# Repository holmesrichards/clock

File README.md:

# Clock

This is a clock synth module in Kosmo format. Features are:

* Rotary encoder to set tempo and other parameters.
* Tap button for a different way to set tempo.
* OLED for display of tempo and settings menu.
* 6 outputs: Beat, clock, clock divided by 2, 4, and 8, and clock divided by arbitrary number (between 1 and 64) with offset.
* Two tempo submodes: INC (increment) mode, to set any whole number of beats per minute (BPM) from 8 to 208, and MM (Maelzel Metronome) mode, to more quickly set standard MM values and generalizations of these from 7.5 (= 60 ÷ 8) to 208 BPM.
* Clock pulses per beat (PPB) variable from 1 to 24.
* Clock pulse width (duty cycle) variable from 5% to 95%.
* Interrupt based timer and encoder codes for accuracy.

## Usage

### Pulses and beats

"Beat" is a musical term, referring to the fundamental unit of rhythm, with usually (not always) a quarter note duration corresponding to one beat. "Tempo" refers to how many beats occur per minute.

Since there are shorter notes than quarter notes, this clock can put out multiple — 4 or 8 or some other number — clock pulses per beat.

### Run mode

The module starts up in **run mode**. Here the display shows the tempo in BPM. In a smaller font at the bottom are also shown  PPB and PPM (pulses per minute, which is just PPB times BPM).

At the left, if the clock is running, there is a dot that flashes once per beat.

At the upper left is shown the tempo submode, INC or MM; see below.

In this mode:

* Turning the encoder clockwise or counterclockwise raises or lowers the tempo.
* Tapping the tactile button sets the tempo to match the time between the last two taps.
* Short pressing the encoder stops or restarts the clock.
* A long encoder press switches between INC and MM submodes.
* A long tactile button press switches to **set mode**.

At startup, the tempo is 120 BPM and there are 4 PPB (so the clock speed is 480 pulses per minute).

#### Tempo submodes

In the INC tempo submode, any whole number of BPM from 8 to 208 may be set. When using the encoder, turning one step clockwise or counterclockwise steps to the next higher or lower whole number. When using the tap button, the tap interval is converted to the nearest whole number BPM.

In the MM submode, the tempo is constrained to a generalized version of the usual Maelzel metronome markings, which are

<pre><span style="font-size: 10px">
|     |     |     |     |     |     |  40 |  42 |  44 |  46 |  48 |  50 |  52 |  54 |  56 |  58 |
|  60 |  63 |  66 |  69 |  72 |  76 |  80 |  84 |  88 |  92 |  96 | 100 | 104 | 108 | 112 | 116 |
| 120 | 126 | 132 | 138 | 144 | 152 | 160 | 168 | 176 | 184 | 192 | 200 | 208 |     |     |     |
</span></pre>

Note each line is 2x the previous, and the steps from one value to the next increase from 2 to 3 to 4 to 6 to 8. Roughly speaking, the gaps between values are about 5% of the value (it's a bit like E48 resistor values); getting from a low value to a high value requires much less encoder turning than in INC mode. The generalized version extends this pattern:

<pre><span style="font-size: 10px">
|   7.5 |   7.875 |   8.25 |   8.625 |   9 |   9.5 |  10 |  10.5 |  11 |  11.5 |  12 |  12.5 |  13 |  13.5 |  14 |  14.5 |
|  15   |  15.75  |  16.5  |  17.25  |  18 |  19   |  20 |  21   |  22 |  23   |  24 |  25   |  26 |  27   |  28 |  29   |
|  30   |  31.5   |  33    |  34.5   |  36 |  38   |  40 |  42   |  44 |  46   |  48 |  50   |  52 |  54   |  56 |  58   |
|  60   |  63     |  66    |  69     |  72 |  76   |  80 |  84   |  88 |  92   |  96 | 100   | 104 | 108   | 112 | 116   |
| 120   | 126     | 132    | 138     | 144 | 152   | 160 | 168   | 176 | 184   | 192 | 200   | 208 |       |     |       |
</span></pre>

In MM submode, when using the encoder, turning one step clockwise or counterclockwise steps to the next higher or lower number in the above list. When using the tap button, the tap interval is converted to the nearest MM value.

At startup, the module is in MM submode.

### Set mode

In this mode four menu lines are shown:

* /N amount
* /N offset
* Pulse/beat
* Width

A cursor on the left edge points to one of these lines. Turning the encoder moves the cursor up or down. Pressing the encoder moves the cursor to the right edge, indicating this line has been selected. Now turning the encoder cycles between available options for that line. Pressing the encoder again moves the cursor back to the left edge.

**/N amt** is the amount of clock division applied on the **Div N** output; there will be an output pulse once every *amt* clock pulses. Any number from 1 through 64 may be selected. At startup, *amt* is 16.

**/N off** is the offset applied to the **Div N** output; output pulses will occur *off* pulses later than they would if *off* were zero. For example, if *amt* is 4 and *off* is 0, output pulses will occur on the same clock pulses on both the **Div 4** and **Div N** outputs, but if *off* is changed to 1, output pulses will occur on the **Div N** output 1 clock pulse after they occur on the **Div 4** output. You can think of the **Div 4** pulses as occurring on the beat while the **Div N** pulses are off the beat. *off* can be set to any value from 0 through *amt*-1. At startup, *off* is 0, and when *amt* is changed, *off* is automatically reset to 0.

**Pulse/beat** is the number of clock pulses per musical beat, or PPB. Any number from 1 through 24 may be selected. At startup, PPB is 4.

**Width** represents the pulse width (duty cycle) of the clock, in percent. Turning the encoder increases or decreases the width in increments of 5%, in the range 5% to 95%. At startup, *width* is 50.

At any time in set mode, a long press on the tactile button switches to run mode.

## Screen blanking

To extend the life of the OLED, whenever more than 1 minute has passed with no control actions (button presses, encoder presses, or encoder turns), the screen is blanked. Any subsequent control action turns the screen back on. If that action is a short button press it will have no other effect (i.e. it will not initiate a tap tempo change). Other control actions while the screen is blank will have their usual effect.

## Credit

I took [Tik-Tak SM](https://create.arduino.cc/projecthub/Synthemafia/modular-synth-clock-module-diy-arduino-sm-tik-tak-bd8ded) as my starting point, but there's not much of it left — I changed and added a lot in both hardware and software.

## Current draw
29 mA +12 V, 0 mA -12 V

## Photos

## Documentation

* [Schematic](Docs/clock.pdf)
* PCB layout: [front](Docs/clock_layout_front.pdf), [back](Docs/clock_layout_back.pdf)
* [BOM](Docs/clock_bom.md)
* [Build notes](Docs/build.md)
* [Blog post](https://analogoutputblog.wordpress.com/2022/11/09/clocking-in/)

## Libraries

The Arduino software uses these libraries:

* TimerOne (from [https://github.com/PaulStoffregen/TimerOne](https://github.com/PaulStoffregen/TimerOne))
* U8g2lib  (from [https://github.com/olikraus/u8g2](https://github.com/olikraus/u8g2))
* DirectIO (from [https://github.com/mmarchetti/DirectIO.git](https://github.com/mmarchetti/DirectIO.git))
* assert (built into Arduino system)

The user must install the first three of these to use the software.

## GitHub repository

* [https://github.com/holmesrichards/clock](https://github.com/holmesrichards/clock)

## Submodules

This repo uses submodules aoKicad and Kosmo_panel, which provide needed libaries for KiCad. To clone:

```
git clone git@github.com:holmesrichards/clock.git
git submodule init
git submodule update
```

Alternatively do

```
git clone --recurse-submodules git@github.com:holmesrichards/clock.git
```

Or if you download the repository as a zip file, you must also click on the "aoKicad" and "Kosmo\_panel" links on the GitHub page (they'll have "@ something" after them) and download them as separate zip files which you can unzip into this repo's aoKicad and Kosmo\_panel directories.

If desired, copy the files from aoKicad and Kosmo\_panel to wherever you prefer (your KiCad user library directory, for instance, if you have one). Then in KiCad, go into Edit Symbols and add symbol libraries 

```
aoKicad/ao_symbols
Kosmo_panel/Kosmo
```
and go into Edit Footprints and add footprint libraries 
```
aoKicad/ao_tht
Kosmo_panel/Kosmo_panel.
```

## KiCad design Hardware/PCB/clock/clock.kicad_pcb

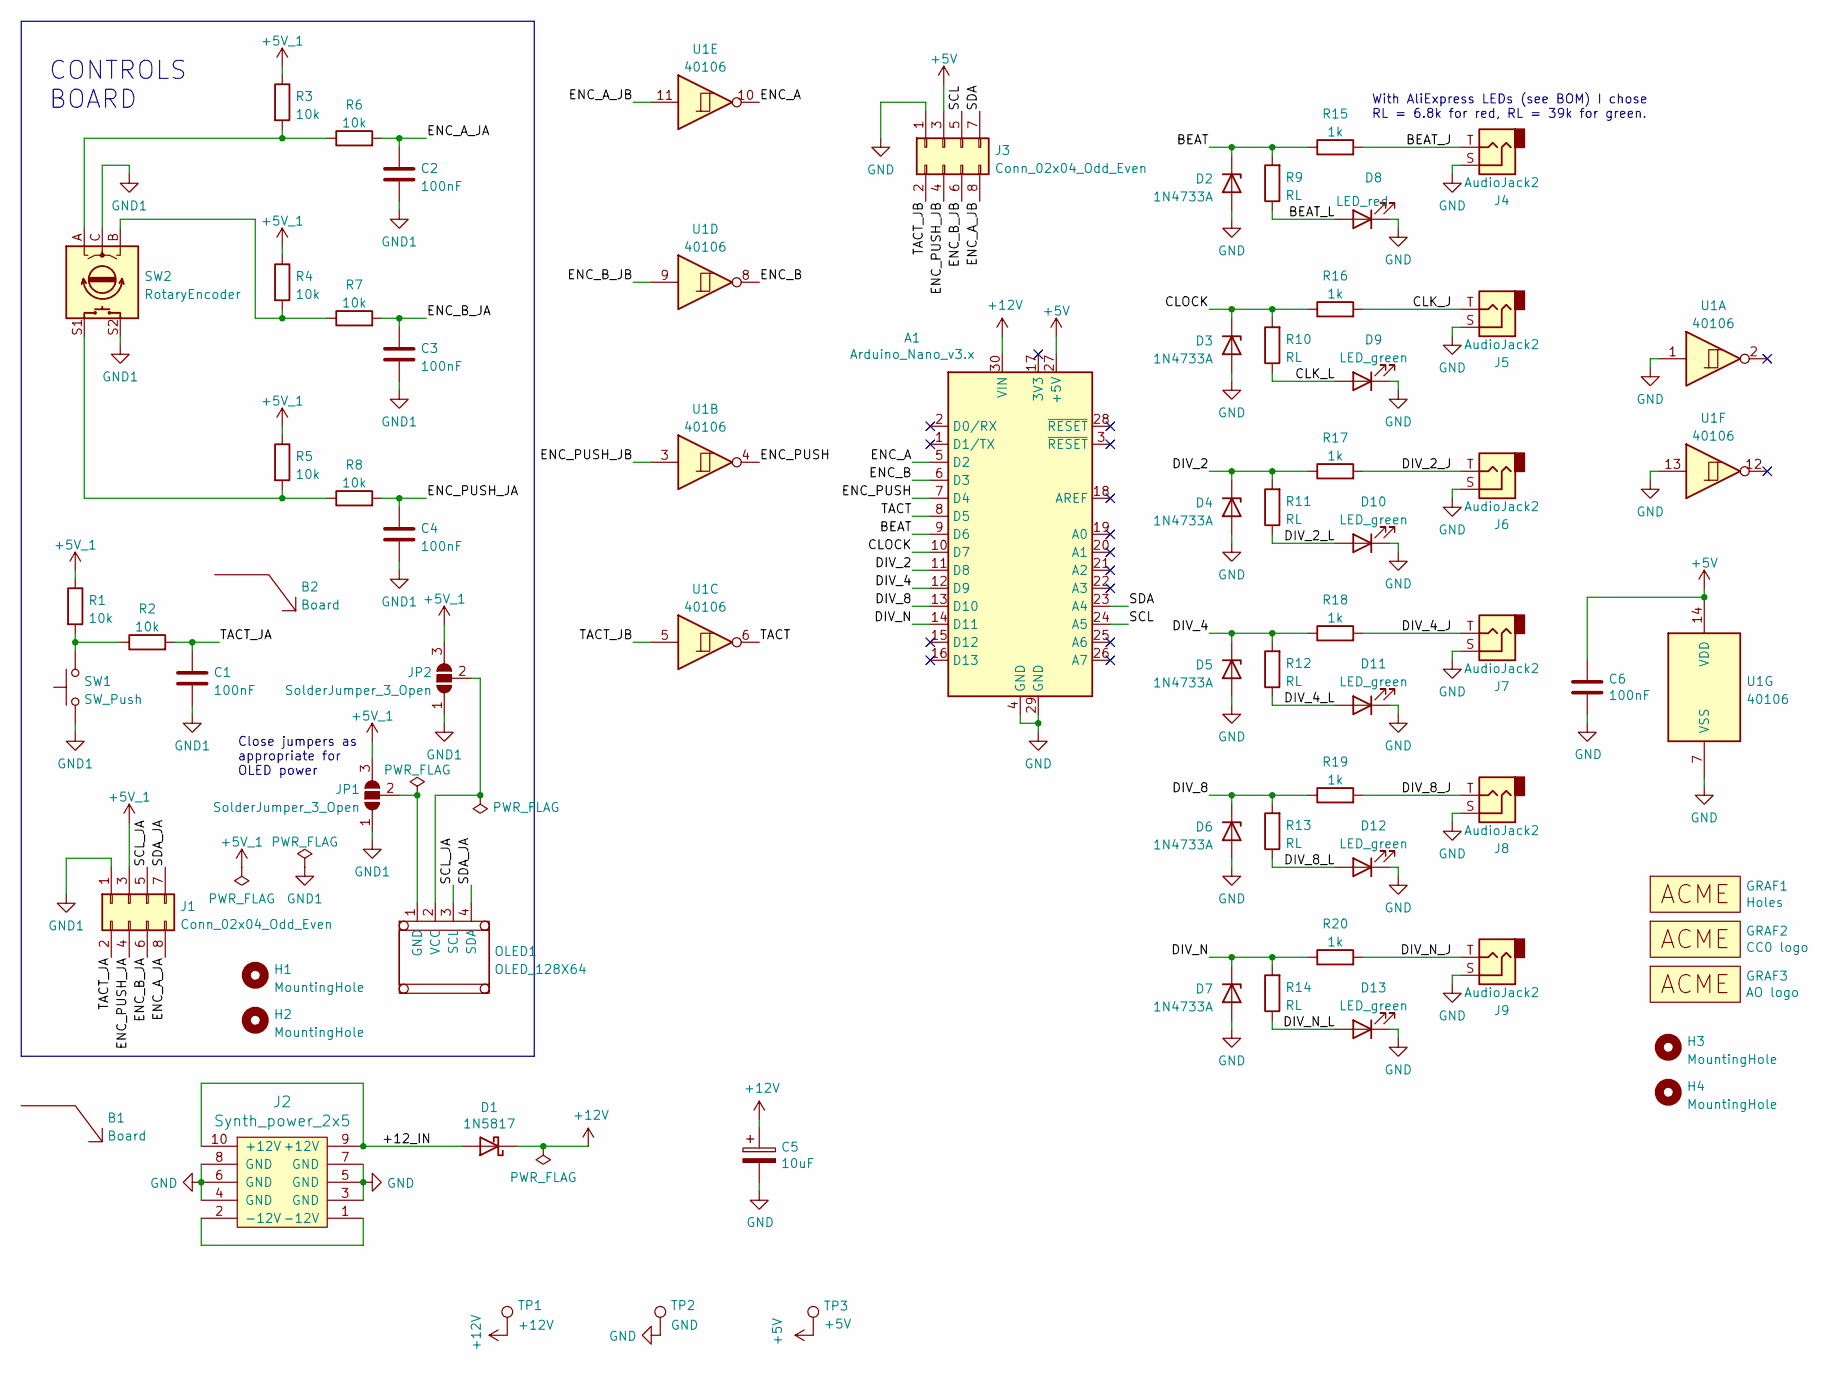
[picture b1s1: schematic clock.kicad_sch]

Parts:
A1: Arduino_Nano_v3.x; Arduino_Nano
B1, B2: Board; Board_Marker
C1, C2, C3, C4, C6: 100nF; C_Disc_D3.0mm_W1.6mm_P2.50mm
C5: 10uF; CP_Radial_D6.3mm_P2.50mm
D1: 1N5817; D_DO-41_SOD81_P10.16mm_Horizontal
D2, D3, D4, D5, D6, D7: 1N4733A; D_DO-41_SOD81_P10.16mm_Horizontal
D8: LED_red; LED_D5.0mm
D9, D10, D11, D12, D13: LED_green; LED_D5.0mm
GRAF1: Holes; clock_panel_holes
GRAF2: CC0 logo; CC0_logo
GRAF3: AO logo; analogoutput_12mm
H1, H2, H3, H4: MountingHole; MountingHole_3.2mm_M3
J1, J3: Conn_02x04_Odd_Even; IDC-Header_2x04_P2.54mm_Vertical
J2: Synth_power_2x5; Power_Header
J4, J5, J6, J7, J8, J9: AudioJack2; Jack_6.35mm_PJ_629HAN_slots
JP1, JP2: SolderJumper_3_Open; SolderJumper-3_P1.3mm_Open_RoundedPad1.0x1.5mm
OLED1: OLED_128X64; OLED_MC130GX
R1, R2, R3, R4, R5, R6, R7, R8: 10k; R_Axial_DIN0204_L3.6mm_D1.6mm_P7.62mm_Horizontal
R9, R10, R11, R12, R13, R14: RL; R_Axial_DIN0204_L3.6mm_D1.6mm_P7.62mm_Horizontal
R15, R16, R17, R18, R19, R20: 1k; R_Axial_DIN0204_L3.6mm_D1.6mm_P7.62mm_Horizontal
SW1: SW_Push; Tactile_E-switch_TL1100F160Q
SW2: RotaryEncoder; RotaryEncoder_Bourns-PEC11R-4xxxF-Sxxxx-Switch_Vertical_H20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
TP1: +12V; TestPoint_THTPad_D1.5mm_Drill0.7mm
TP2: GND; TestPoint_THTPad_D1.5mm_Drill0.7mm
TP3: +5V; TestPoint_THTPad_D1.5mm_Drill0.7mm
U1: 40106; DIP-14_W7.62mm_Socket_LongPads

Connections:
+5V: A1.27 (+5V), C6.1, J3.3, TP3.1, U1.14 (VDD)
+5V_1: J1.3, JP1.3 (B), JP2.3 (B), R1.1, R3.1, R4.1, R5.1
+12V: A1.30 (VIN), C5.1, D1.1 (K), TP1.1
/+12_IN: D1.2 (A), J2.9 (+12V), J2.10 (+12V)
/BEAT: A1.9 (D6), D2.1 (K), R9.2, R15.1
/BEAT_J: J4.T, R15.2
/BEAT_L: D8.2 (A), R9.1
/CLK_J: J5.T, R16.2
/CLK_L: D9.2 (A), R10.1
/CLOCK: A1.10 (D7), D3.1 (K), R10.2, R16.1
/DIV_2: A1.11 (D8), D4.1 (K), R11.2, R17.1
/DIV_2_J: J6.T, R17.2
/DIV_2_L: D10.2 (A), R11.1
/DIV_4: A1.12 (D9), D5.1 (K), R12.2, R18.1
/DIV_4_J: J7.T, R18.2
/DIV_4_L: D11.2 (A), R12.1
/DIV_8: A1.13 (D10), D6.1 (K), R13.2, R19.1
/DIV_8_J: J8.T, R19.2
/DIV_8_L: D12.2 (A), R13.1
/DIV_N: A1.14 (D11), D7.1 (K), R14.2, R20.1
/DIV_N_J: J9.T, R20.2
/DIV_N_L: D13.2 (A), R14.1
/ENC_A: A1.5 (D2), U1.10
/ENC_A_JA: C2.1, J1.8, R6.2
/ENC_A_JB: J3.8, U1.11
/ENC_B: A1.6 (D3), U1.8
/ENC_B_JA: C3.1, J1.6, R7.2
/ENC_B_JB: J3.6, U1.9
/ENC_PUSH: A1.7 (D4), U1.4
/ENC_PUSH_JA: C4.1, J1.4, R8.2
/ENC_PUSH_JB: J3.4, U1.3
/SCL: A1.24 (A5), J3.5
/SCL_JA: J1.5, OLED1.3 (SCL)
/SDA: A1.23 (A4), J3.7
/SDA_JA: J1.7, OLED1.4 (SDA)
/TACT: A1.8 (D5), U1.6
/TACT_JA: C1.1, J1.2, R2.2
/TACT_JB: J3.2, U1.5
GND: A1.4 (GND), A1.29 (GND), C5.2, C6.2, D2.2 (A), D3.2 (A), D4.2 (A), D5.2 (A), D6.2 (A), D7.2 (A), D8.1 (K), D9.1 (K), D10.1 (K), D11.1 (K), D12.1 (K), D13.1 (K), J2.3 (GND), J2.4 (GND), J2.5 (GND), J2.6 (GND), J2.7 (GND), J2.8 (GND), J3.1, J4.S, J5.S, J6.S, J7.S, J8.S, J9.S, TP2.1, U1.1, U1.7 (VSS), U1.13
GND1: C1.2, C2.2, C3.2, C4.2, J1.1, JP1.1 (A), JP2.1 (A), SW1.1, SW2.C, SW2.S2
unnamed: J2.1 (-12V), J2.2 (-12V)
unnamed: JP1.2 (C), OLED1.1 (GND)
unnamed: JP2.2 (C), OLED1.2 (VCC)
unnamed: R1.2, R2.1, SW1.2
unnamed: R3.2, R6.1, SW2.A
unnamed: R4.2, R7.1, SW2.B
unnamed: R5.2, R8.1, SW2.S1

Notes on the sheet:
Close jumpers as appropriate for OLED power
With AliExpress LEDs (see BOM) I chose RL = 6.8k for red, RL = 39k for green.
CONTROLS BOARD

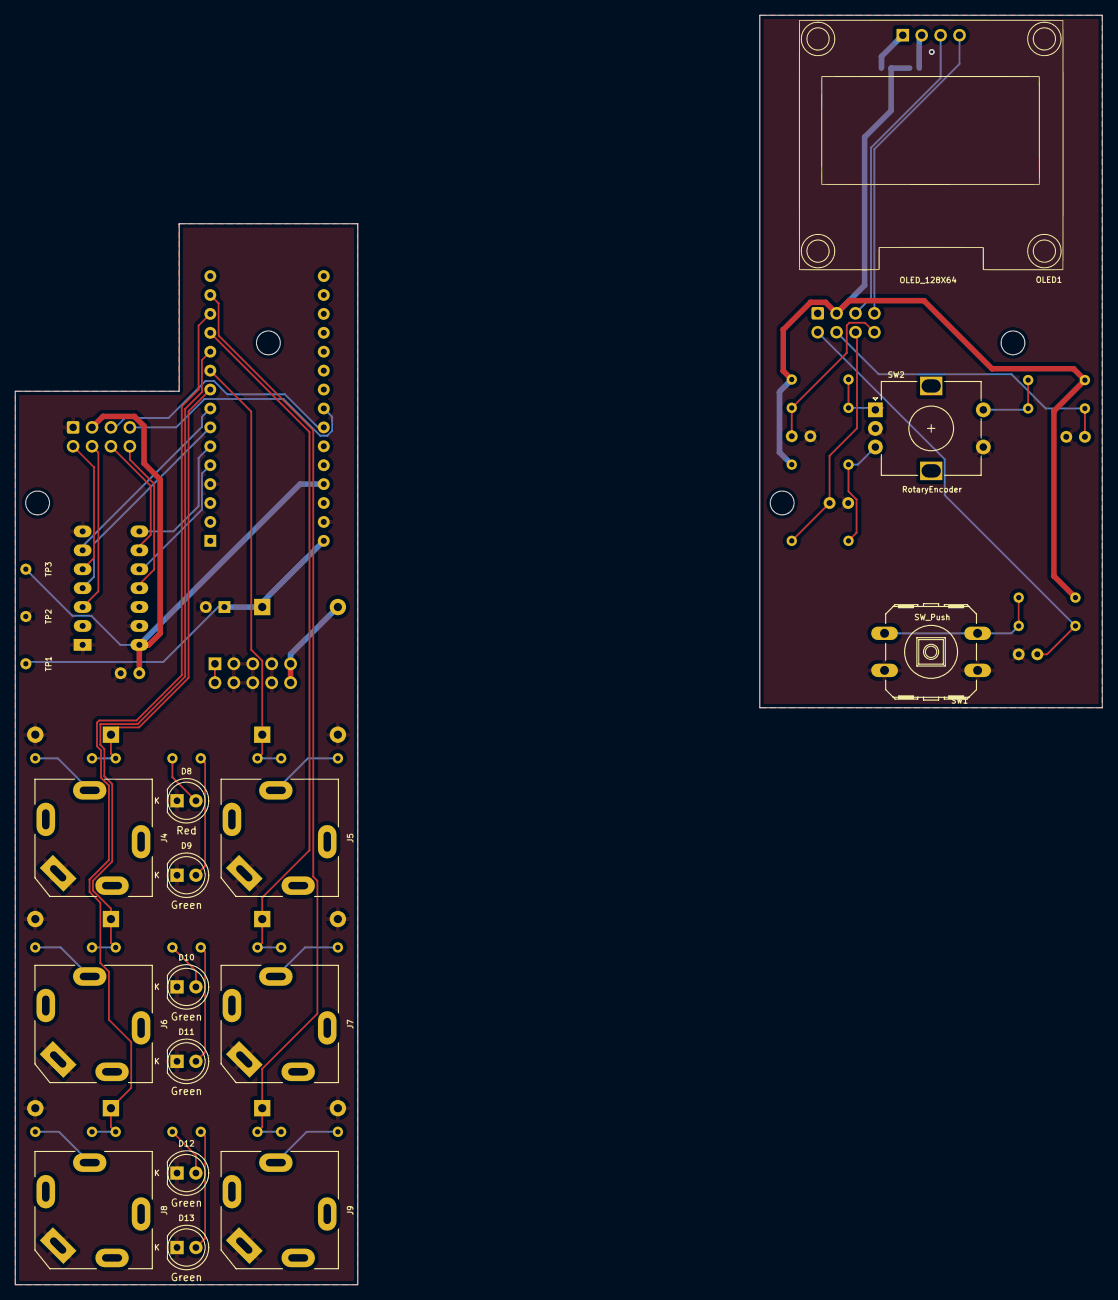
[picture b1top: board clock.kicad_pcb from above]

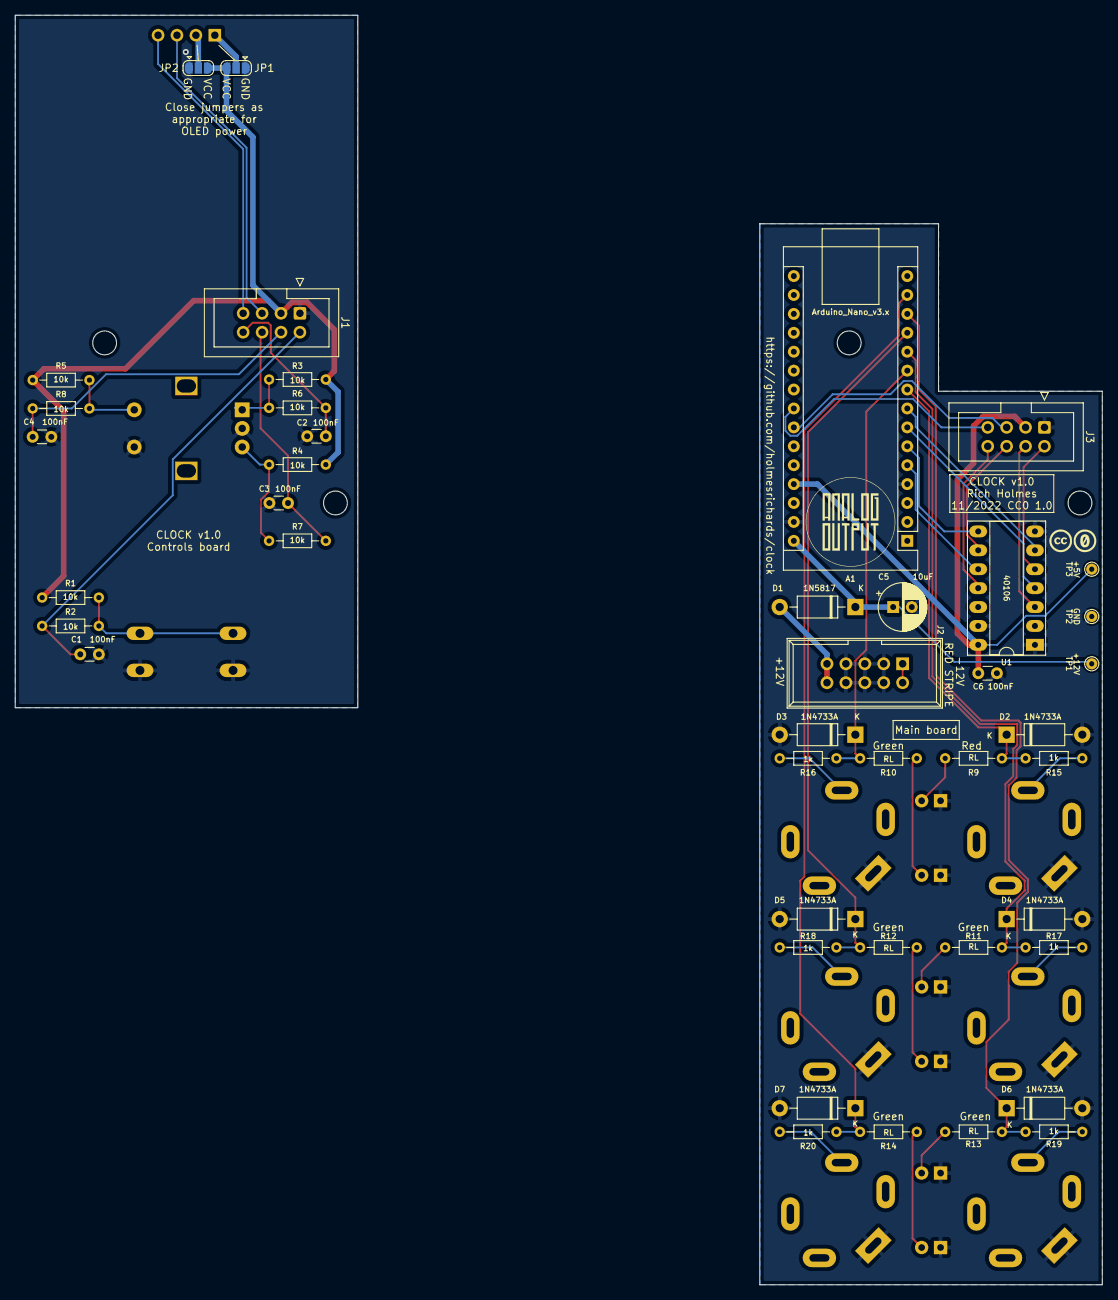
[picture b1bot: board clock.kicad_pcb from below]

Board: 2 copper layers, 146.0 x 170.5 mm, 67 parts (47 on the bottom side), 47 nets.

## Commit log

2021-09-09 Clean up libraries, Schottky footprint update
2021-09-15 SVG decontamination
2021-11-26 Revise panel
2021-11-26 Notes with evolving design ideas. Ignore folder.
2021-12-02 Panel art
2021-12-05 README edit
2021-12-22 revise notes
2021-12-25 README
2022-02-01 Better .gitignore
2022-05-19 Revisions to interface, panel update
2022-05-19 Panel update
2022-05-19 Initial schematic and software
2022-05-19 Update interface ideas
2022-05-19 Update schematic
2022-05-20 Schematic, sketch development
2022-05-21 Invert clock in; fill in README; software improvements; rm notes
2022-05-22 Initial layout, README update, software cleanup
2022-05-22 Only update OLED items that need it
2022-05-22 Should prevent meltdown if millis() wraps around
2022-05-22 README updates, MM range adjusted and millis overflow handling corrected
2022-05-22 Layout revisions
2022-05-24 More accurate timing and rm stupidity on wraparound
2022-05-25 More correct wraparound safe code, I think
2022-05-25 More correct wraparound safe code, I think, no really I mean it this time
2022-05-25 Add pulses per beat options
2022-05-25 Go to 100 us interrupt interval, to handle 208 BPM * 24 PPB reasonably well
2022-05-26 Add Zeners, reallocate XORs
2022-05-26 Unix line endings, interrupt driven encoder, beat flasher
2022-05-26 README update; fix set display handling when ext clock enabled
2022-05-26 Rearrange digital pins (for encoder to interrupt pin 2)
2022-05-26 Rename INT submode to INC to reduce confusion with INT clock
2022-05-27 rm external clock, add beat output
2022-05-27 Reset counts when changing division; update schematic and layout with beat output, no ext clock, and unimpeded Nano USB
2022-05-27 Beat output on panel
2022-05-27 Add PPM to run display (and move submode)
2022-05-28 PCB adjustments
2022-05-28 Suppress silk
2022-05-28 Set BEAT pin to OUTPUT
2022-05-28 LED notes
2022-05-28 LED notes on sch
2022-06-10 LED correction
2022-06-20 Kosmo_panel branch fix
2022-07-10 PCB touch ups, panel
2022-07-10 typo; OLED panel footprint
2022-07-10 Jumpers for OLED power
2022-07-10 rm KiCad 5 files
2022-07-27 AliExpress LEDs and their suitable resistances
2022-11-05 pre fab updates, gerbers, schem pdf
2022-11-05 Fix wayward trace; add silk labels for LEDs and RLs
2022-11-06 build.md
2022-11-07 Correct switch footprint
2022-11-07 Screen blanking
2022-11-08 No OLED mounting holes
2022-11-08 build notes
2022-11-08 Documentation and library updates
2022-11-08 LICENSE
2022-11-08 Add version # to PCBs; update errata section in build.md
2022-11-08 new Gerbers
2022-11-08 Correct README
2022-11-08 README tweak
2022-11-08 non obsolete image
2022-11-08 BOM corrections
2022-11-08 panel svg update
2022-11-09 Link to blog post
2022-11-11 Tactile switch PN and SKU were reversed
2022-11-27 rm debug prints

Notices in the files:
Hardware/PCB/clock/clock.kicad_pcb:
11/2022 CC0 1.0
